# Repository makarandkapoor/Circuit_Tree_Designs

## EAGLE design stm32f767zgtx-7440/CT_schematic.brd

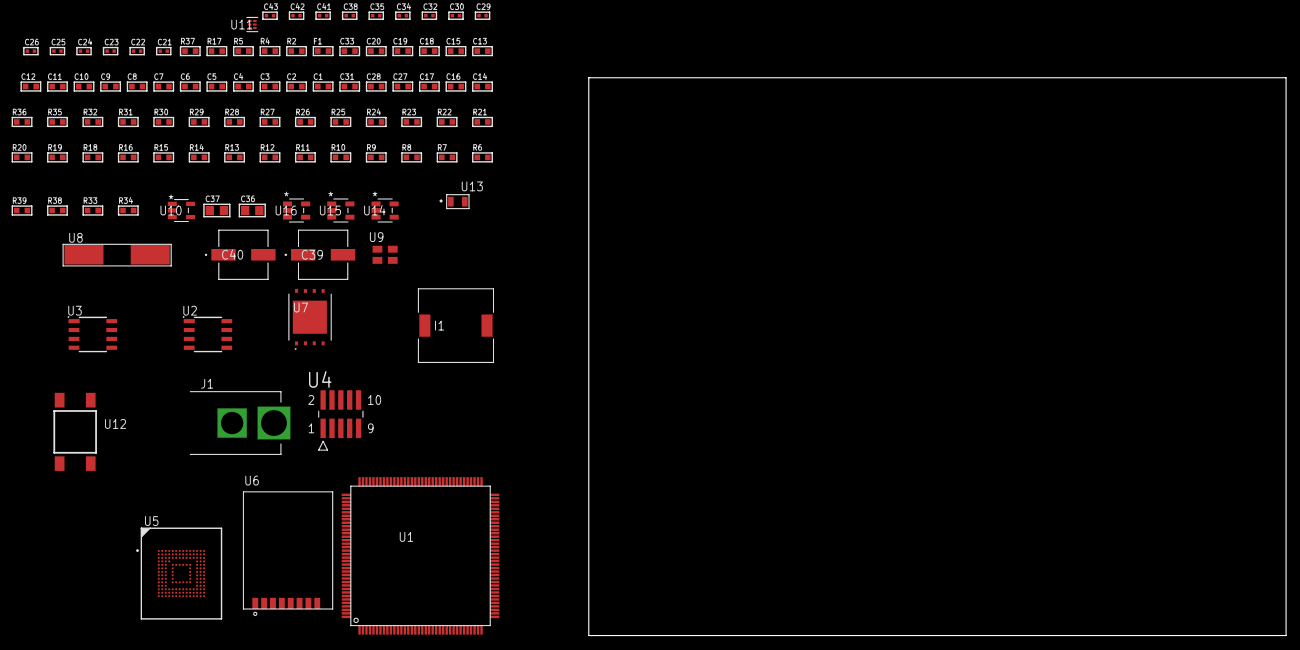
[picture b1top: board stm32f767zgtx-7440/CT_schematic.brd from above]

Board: 2 copper layers, 100.0 x 80.0 mm, 99 parts (0 on the bottom side), 60 nets, no tracks yet.

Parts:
C1, C19, C33: 1e-06; C0603
C2, C3, C4, C5, C6, C7, C8, C9, C10, C11, C12, C13, C15, C20: 1e-07; C0603
C14: 4.7e-06; C0603
C16, C17, C27, C28, C31: 2.2e-06; C0603
C18: 1e-08; C0603
C21, C22: 1e-11; C0402
C23, C24, C34, C35, C41, C42, C43: 1e-08; C0402
C25, C26, C29, C30, C32, C38: 1e-07; C0402
C36, C37: 1e-05; C0805
C39, C40: 0.0001; EXV-9H
F1: 240.0; L0603
I1: 5.2e-06; DR1040
J1: PJ-037B; PJ-037B_PACKAGE
R2: 1000.0; R0603
R4, R5: 4700.0; R0603
R6, R7, R8, R9, R10, R11, R12, R13, R14, R15, R16, R28, R29, R30, R31, R32, R35, R36: 10000.0; R0603
R17: 5.0; R0603
R18, R19, R20, R21, R22, R23, R24, R25, R26, R27: 34000.0; R0603
R33: 220000.0; R0603
R34: 1000000.0; R0603
R37: 9100.0; R0603
R38: 680000.0; R0603
R39: 120000.0; R0603
U1: STM32F767ZGT6; LQFP144
U2: AT25010B-SSHL-T; SOIC-8
U3: AT25M02-SSHD-T; SOIC-8
U4: FTSH-105-01-L-DV-K; SAMTEC_FTSH-105-01-L-DV-K
U5: mtfc4gmcdm; TFBGA-153
U6: RFM75-S
U7: S25FL128SDPNFI001; WNG008
U8: ABLS-25.000MHZ-B2F-T
U9: ASEK-32.768KHz-ECST; ASEK
U10: ltc3406es5; TSOT-23-5
U11: TPS3895ADRYR; SON-6
U12: 4-1437565-2; SW_4-1437565-2
U13: Q65110A2395; LGM67K-G1J2-24-Z
U14, U15, U16: nc7sz125m5x; NC7SZ125M5X

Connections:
CLK_CRYSTAL_U1_23: C21.1, U1.23, U8.1
CLK_CRYSTAL_U1_24: C22.1, U1.24, U8.2
CLK_U1_8: U1.8, U9.3
GND: C1.2, C2.2, C3.2, C4.2, C5.2, C6.2, C7.2, C8.2, C9.2, C10.2, C11.2, C12.2, C13.2, C14.2, C15.2, C16.2, C17.2, C18.2, C19.2, C20.2, C21.2, C22.2, C23.2, C24.2, C25.2, C26.2, C27.2, C28.2, C29.2, C30.2, C31.2, C32.2, C33.2, C34.2, C35.2, C36.2, C37.1, C37.2, C38.2, C39.2, C40.2, C41.2, C42.2, C43.2, J1.2, R2.2, R6.2, R17.2, R33.2, R37.2, R39.2, U1.16, U1.31, U1.38, U1.51, U1.61, U1.83, U1.94, U1.107, U1.120, U1.130, U2.4, U3.4, U4.3, U4.5, U5.C4, U5.E7, U5.G5, U5.H10, U5.K8, U5.N2, U5.N5, U5.P4, U5.P6, U6.1, U7.4, U7.PAD, U9.2, U10.2, U11.2, U13.C, U14.2, U14.3, U15.1, U15.3, U16.1, U16.3
NET_U1_25: R5.1, U1.25, U16.4
NET_U1_33: C18.1, C19.1, F1.1, U1.32, U1.33
NET_U1_71: C16.1, U1.71
NET_U1_106: C17.1, U1.106
NET_U1_138: R6.1, U1.138
NET_U1_142: U12.3, U12.4
NET_U1_143: R7.1, U1.143
NET_U2_3: R8.1, U2.3
NET_U2_7: R10.1, U2.7
NET_U3_3: R11.1, U3.3
NET_U3_7: R13.1, U3.7
NET_U4_9: R17.1, U4.9
NET_U5_C2: C28.1, C29.1, U5.C2
NET_U5_K5: R4.1, U5.K5, U15.4
NET_U6_3: R28.1, U6.3
NET_U7_3: R30.1, U7.3
NET_U7_7: R32.1, U7.7
NET_U10_3: I1.1, U10.3
NET_U10_5: R33.1, R34.1, U10.5
NET_U10_ATNET_3: I1.2, R34.2
NET_U11_1: R36.1, R37.1, U11.1
NET_U11_3: R38.2, R39.1, U11.3
NET_U11_4: R35.1, U11.4, U14.4, U15.2, U16.2
NET_U12_1: R2.1, U12.1, U12.2
PROC_SDMMC1_CK: R27.1, U1.113, U5.M6
PROC_SDMMC1_CMD: R26.1, U1.116, U5.M5
PROC_SDMMC1_D0: R18.1, U1.98, U5.A3
PROC_SDMMC1_D1: R19.1, U1.99, U5.A4
PROC_SDMMC1_D2: R20.1, U1.111, U5.A5
PROC_SDMMC1_D3: R21.1, U1.112, U5.B2
PROC_SDMMC1_D4: R22.1, U1.139, U5.B3
PROC_SDMMC1_D5: R23.1, U1.140, U5.B4
PROC_SDMMC1_D6: R24.1, U1.96, U5.B5
PROC_SDMMC1_D7: R25.1, U1.97, U5.B6
PROC_SPI1_MISO: U1.42, U6.7
PROC_SPI1_MOSI: U1.43, U6.6
PROC_SPI1_NSS: R29.1, U1.40, U6.4
PROC_SPI1_SCK: U1.41, U6.5
PROC_SPI2_MISO: U1.28, U3.2
PROC_SPI2_MOSI: U1.27, U3.5
PROC_SPI2_NSS: R12.1, U1.73, U3.1
PROC_SPI2_SCK: U1.69, U3.6
PROC_SPI4_MISO: U1.4, U7.2
PROC_SPI4_MOSI: U1.5, U7.5
PROC_SPI4_NSS: R31.1, U1.3, U7.1
PROC_SPI4_SCK: U1.1, U7.6
PROC_SPI5_MISO: U1.20, U2.2
PROC_SPI5_MOSI: U1.21, U2.5
PROC_SPI5_NSS: R9.1, U1.18, U2.1
PROC_SPI5_SCK: U1.19, U2.6
PROC_SYS_JTCK_SWCLK: R15.1, U1.109, U4.4
PROC_SYS_JTDO_SWO: U1.133, U4.6
PROC_SYS_JTMS_SWDIO: R16.1, U1.105, U4.2
RST_OUT_U4_JTAG_RST_B: R14.1, U4.10, U14.1
VCC_S1_5V4: C36.1, C39.1, C40.1, J1.1, U10.4
VCC_TIER1_3V3: C1.1, C2.1, C3.1, C4.1, C5.1, C6.1, C7.1, C8.1, C9.1, C10.1, C11.1, C12.1, C13.1, C14.1, C15.1, C20.1, C23.1, C24.1, C25.1, C26.1, C27.1, C30.1, C31.1, C32.1, C33.1, C34.1, C35.1, C37.2, C38.1, C41.1, C42.1, C43.1, F1.2, I1.2, R4.2, R5.2, R7.2, R8.2, R9.2, R10.2, R11.2, R12.2, R13.2, R14.2, R15.2, R16.2, R18.2, R19.2, R20.2, R21.2, R22.2, R23.2, R24.2, R25.2, R26.2, R27.2, R28.2, R29.2, R30.2, R31.2, R32.2, R34.2, R35.2, R36.2, R38.1, U1.6, U1.17, U1.30, U1.39, U1.52, U1.62, U1.72, U1.84, U1.95, U1.108, U1.121, U1.131, U1.144, U2.8, U3.8, U4.1, U5.C6, U5.E6, U5.F5, U5.J10, U5.K9, U5.M4, U5.N4, U5.P3, U5.P5, U6.2, U7.8, U9.4, U11.6, U14.5, U15.5, U16.5

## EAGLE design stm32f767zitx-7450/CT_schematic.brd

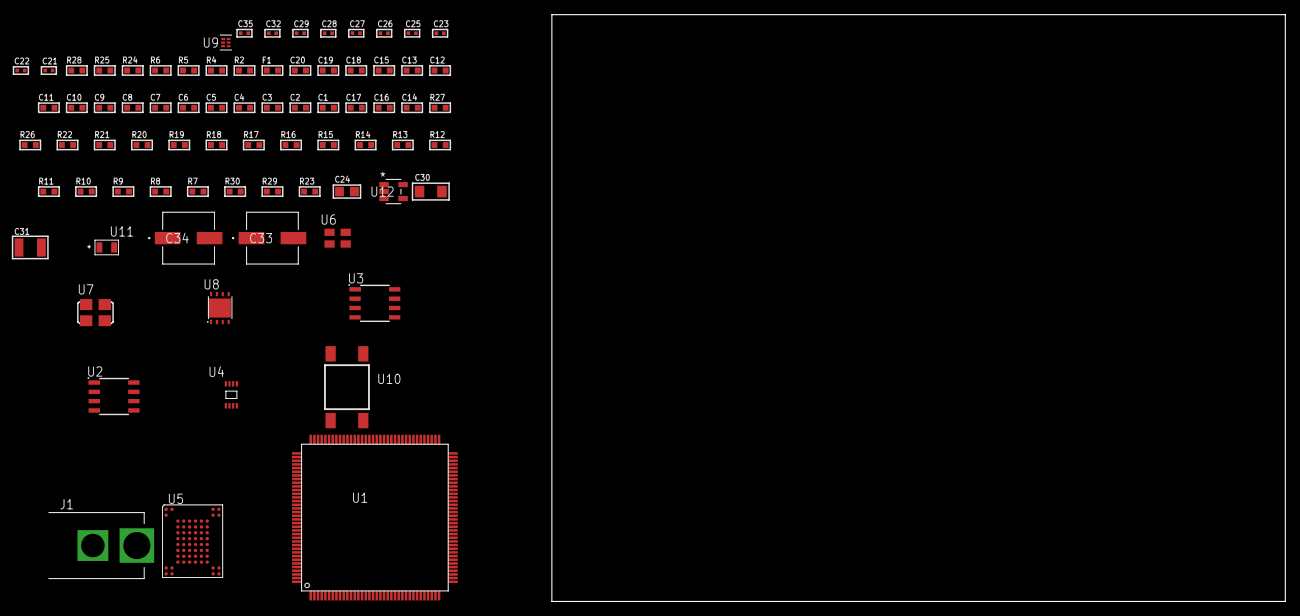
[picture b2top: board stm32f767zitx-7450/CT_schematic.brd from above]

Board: 2 copper layers, 100.0 x 80.0 mm, 77 parts (0 on the bottom side), 51 nets, no tracks yet.

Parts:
C1, C19: 1e-06; C0603
C2, C3, C4, C5, C6, C7, C8, C9, C10, C11, C12, C13, C15, C20: 1e-07; C0603
C14: 4.7e-06; C0603
C16, C17: 2.2e-06; C0603
C18: 1e-08; C0603
C21, C22, C23, C27, C28, C29, C35: 1e-08; C0402
C24: 1e-05; C0805
C25, C26, C32: 1e-07; C0402
C30: 1e-05; C1206
C31: 1e-05; C1210
C33, C34: 0.0001; EXV-9H
F1: 240.0; L0603
J1: PJ-037B; PJ-037B_PACKAGE
R2, R25: 1000.0; R0603
R4: 4700.0; R0603
R5, R6: 2200.0; R0603
R7, R8, R9, R10, R11, R12, R13, R14, R15, R16, R17, R18, R19, R20, R21, R22, R26, R27: 10000.0; R0603
R23: 100000.0; R0603
R24: 2231.0; R0603
R28: 9100.0; R0603
R29: 680000.0; R0603
R30: 120000.0; R0603
U1: STM32F767ZIT6; LQFP144
U2: AT25256B-SSHL-T; SOIC-8
U3: AT25M01-SSHM-T; SOIC-8
U4: 24AA128T-I/MNY; TDFN-8/6MM
U5: TH58NVG3S0HBAI4
U6: ASEK-32.768KHz-ECST; ASEK
U7: ASFL1-25MHZ-NCS; ASFL1
U8: LP3878SDX-ADJ/NOPB; WSON-8
U9: TPS3895ADRYR; SON-6
U10: 4-1437565-2; SW_4-1437565-2
U11: Q65110A2395; LGM67K-G1J2-24-Z
U12: nc7sz125m5x; NC7SZ125M5X

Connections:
CLK_U1_8: U1.8, U6.3
CLK_U1_23: U1.23, U7.3
GND: C1.2, C2.2, C3.2, C4.2, C5.2, C6.2, C7.2, C8.2, C9.2, C10.2, C11.2, C12.2, C13.2, C14.2, C15.2, C16.2, C17.2, C18.2, C19.2, C20.2, C21.2, C22.2, C23.2, C24.2, C25.2, C26.2, C27.2, C28.2, C29.2, C30.2, C31.2, C32.2, C33.2, C34.2, C35.2, J1.2, R2.2, R7.2, R15.2, R25.2, R28.2, R30.2, U1.16, U1.31, U1.38, U1.51, U1.61, U1.83, U1.94, U1.107, U1.120, U1.130, U2.4, U3.4, U4.4, U4.7, U5.C5, U5.K3, U5.K8, U6.2, U7.2, U8.3, U8.PAD, U9.2, U11.C, U12.1, U12.3
NET_U1_25: R4.1, U1.25, U12.4
NET_U1_33: C18.1, C19.1, F1.1, U1.32, U1.33
NET_U1_71: C16.1, U1.71
NET_U1_106: C17.1, U1.106
NET_U1_136: R5.1, U1.136, U4.6
NET_U1_137: R6.1, U1.137, U4.5
NET_U1_138: R7.1, U1.138
NET_U1_142: U10.3, U10.4
NET_U1_143: R8.1, U1.143
NET_U2_3: R9.1, U2.3
NET_U2_7: R11.1, U2.7
NET_U3_3: R12.1, U3.3
NET_U3_7: R14.1, U3.7
NET_U4_1: R15.1, U4.1
NET_U4_2: R16.1, U4.2
NET_U4_3: R17.1, U4.3
NET_U5_C3: R21.1, U5.C3
NET_U8_1: C29.1, U8.1
NET_U8_6: R24.2, R25.1, U8.6
NET_U8_8: R23.1, U8.8
NET_U9_1: R27.1, R28.1, U9.1
NET_U9_3: R29.2, R30.1, U9.3
NET_U9_4: R26.1, U9.4, U12.2
NET_U10_1: R2.1, U10.1, U10.2
PROC_FMC_A16: U1.80, U5.D5
PROC_FMC_A17: U1.81, U5.C4
PROC_FMC_D0: U1.85, U5.H4
PROC_FMC_D1: U1.86, U5.J4
PROC_FMC_D2: U1.114, U5.K4
PROC_FMC_D3: U1.115, U5.K5
PROC_FMC_D4: U1.58, U5.K6
PROC_FMC_D5: U1.59, U5.J7
PROC_FMC_D6: U1.60, U5.K7
PROC_FMC_D7: U1.63, U5.J8
PROC_FMC_INT: R22.1, U1.92, U5.C8
PROC_FMC_NCE: R18.1, U1.98, U5.C6
PROC_FMC_NOE: R19.1, U1.118, U5.D4
PROC_FMC_NWE: R20.1, U1.119, U5.C7
PROC_SPI1_MISO: U1.42, U2.2
PROC_SPI1_MOSI: U1.43, U2.5
PROC_SPI1_NSS: R10.1, U1.40, U2.1
PROC_SPI1_SCK: U1.41, U2.6
PROC_SPI2_MISO: U1.28, U3.2
PROC_SPI2_MOSI: U1.27, U3.5
PROC_SPI2_NSS: R13.1, U1.73, U3.1
PROC_SPI2_SCK: U1.69, U3.6
VCC_S1_6V5: C30.1, C33.1, C34.1, J1.1, R23.2, U8.4
VCC_TIER1_3V3: C1.1, C2.1, C3.1, C4.1, C5.1, C6.1, C7.1, C8.1, C9.1, C10.1, C11.1, C12.1, C13.1, C14.1, C15.1, C20.1, C21.1, C22.1, C23.1, C24.1, C25.1, C26.1, C27.1, C28.1, C31.1, C32.1, C35.1, F1.2, R4.2, R5.2, R6.2, R8.2, R9.2, R10.2, R11.2, R12.2, R13.2, R14.2, R16.2, R17.2, R18.2, R19.2, R20.2, R21.2, R22.2, R24.1, R26.2, R27.2, R29.1, U1.6, U1.17, U1.30, U1.39, U1.52, U1.62, U1.72, U1.84, U1.95, U1.108, U1.121, U1.131, U1.144, U2.8, U3.8, U4.8, U5.H8, U5.J6, U6.4, U7.4, U8.5, U9.6, U12.5

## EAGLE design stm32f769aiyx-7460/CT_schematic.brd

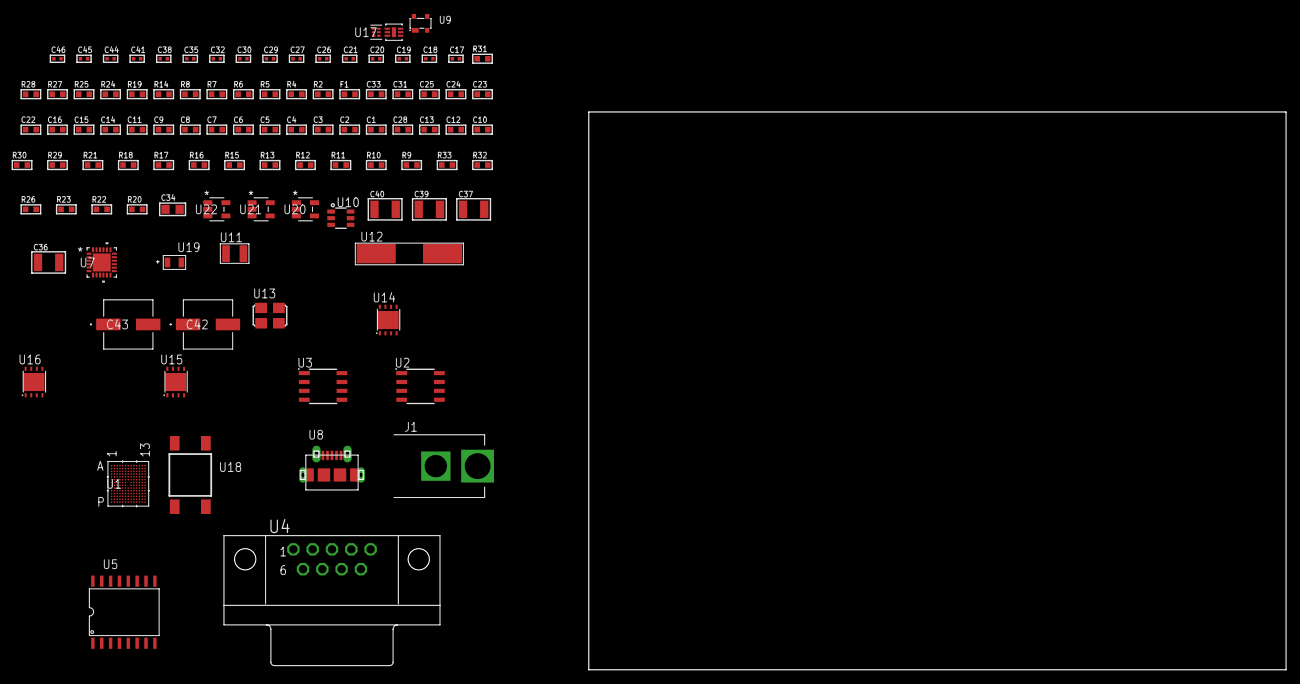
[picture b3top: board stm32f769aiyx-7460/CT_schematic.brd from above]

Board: 2 copper layers, 101 parts (0 on the bottom side), 70 nets, no tracks yet.

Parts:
C1, C15, C22, C23, C24, C25, C31: 1e-06; C0603
C2, C3, C4, C5, C6, C7, C8, C9, C11, C16: 1e-07; C0603
C10: 4.7e-06; C0603
C12, C13, C28: 2.2e-06; C0603
C14: 1e-08; C0603
C17, C18, C19, C20: 1e-11; C0402
C21, C27, C29, C30, C32, C35, C38, C44, C45, C46: 1e-08; C0402
C26, C41: 1e-07; C0402
C33: 8e-07; R0603
C34: 1e-05; C0805
C36, C37, C39, C40: 1e-05; C1210
C42, C43: 0.0001; EXV-9H
F1: 240.0; L0603
J1: PJ-037B; PJ-037B_PACKAGE
R2, R25, R28: 1000.0; R0603
R4, R5, R6: 4700.0; R0603
R7, R8: 2200.0; R0603
R9, R10, R11, R12, R13, R15, R16, R17, R29, R30: 10000.0; R0603
R14: 120.0; R0603
R18: 47000.0; R0603
R19: 8060.0; R0603
R20, R22, R23, R26: 100000.0; R0603
R21: 36000.0; R0603
R24: 2231.0; R0603
R27: 3900.0; R0603
R31: 9100.0; R0603
R32: 680000.0; R0603
R33: 120000.0; R0603
U1: STM32F769AIY6TR; WLCSP180
U2: AT25040B-SSHL-T; SOIC-8
U3: MCP2562-E/SN; SOIC-8
U4: 182-009-113R531; 182-009-MALE
U5: S25FL128SDSMFI000
U6: SI7006-A20-IM; DFN-6
U7: USB3317C-CP-TR; QFN-24
U8: 47590-0001; MICRO_USB_AB
U9: prtr5v0u2ax; SOT143B
U10: MAX4995AAUT+T; SOT-23-6
U11: ABS07-32.768KHZ-7-T
U12: ABLS-25.000MHZ-B2F-T
U13: ASFL1-26MHZ-NCS; ASFL1
U14: LP2951ACSDX/NOPB; WSON-8
U15, U16: LP3878SDX-ADJ/NOPB; WSON-8
U17: TPS3895ADRYR; SON-6
U18: 4-1437565-2; SW_4-1437565-2
U19: Q65110A2395; LGM67K-G1J2-24-Z
U20, U21, U22: nc7sz125m5x; NC7SZ125M5X

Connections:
CLK_CRYSTAL_U1_E12: C17.1, U1.E12, U11.1
CLK_CRYSTAL_U1_E13: C18.1, U1.E13, U11.2
CLK_CRYSTAL_U1_K12: C19.1, U1.K12, U12.1
CLK_CRYSTAL_U1_K13: C20.1, U1.K13, U12.2
CLK_U7_23: U7.23, U13.3
GND: C1.2, C2.2, C3.2, C4.2, C5.2, C6.2, C7.2, C8.2, C9.2, C10.2, C11.2, C12.2, C13.2, C14.2, C15.2, C16.2, C17.2, C18.2, C19.2, C20.2, C21.2, C22.2, C23.2, C24.2, C25.2, C26.2, C27.2, C28.2, C29.2, C30.2, C31.2, C32.2, C33.2, C34.2, C35.2, C36.2, C37.2, C38.2, C39.2, C40.2, C41.2, C42.2, C43.2, C44.2, C45.2, C46.2, J1.2, R2.2, R9.2, R18.2, R19.2, R22.2, R25.2, R28.2, R31.2, R33.2, U1.A8, U1.A11, U1.B6, U1.C2, U1.F1, U1.F13, U1.H5, U1.J9, U1.J13, U1.M1, U1.M11, U1.N4, U1.N5, U1.P9, U2.4, U3.2, U3.8, U4.5, U5.10, U6.2, U6.7, U7.25, U8.5, U8.6, U8.7, U8.8, U8.9, U9.1, U10.2, U13.2, U14.3, U14.4, U14.PAD, U15.3, U15.PAD, U16.3, U16.PAD, U17.2, U19.C, U20.1, U20.3, U21.1, U21.3, U22.1, U22.3
NET_U1_A10: R9.1, U1.A10
NET_U1_C1: C13.1, U1.C1
NET_U1_C8: R8.1, U1.C8, U6.1
NET_U1_C10: R10.1, U1.C10
NET_U1_E9: R7.1, U1.E9, U6.6
NET_U1_L11: R5.1, U1.L11, U21.4
NET_U1_M12: C14.1, C15.1, F1.1, U1.M12
NET_U1_P5: C12.1, U1.P5
NET_U1_P8: U18.3, U18.4
NET_U2_3: R11.1, U2.3
NET_U2_7: R13.1, U2.7
NET_U3_6: R14.2, U3.6
NET_U4_2: R14.2, U3.6, U4.2
NET_U4_3: R14.1, U3.7, U4.3
NET_U5_3: R4.1, U5.3, U20.4
NET_U7_4: C28.1, U7.4
NET_U7_22: R6.1, U7.22, U22.4
NET_U7_24: R19.1, U7.24
NET_U8_1: C31.1, U7.2, U8.1, U9.4, U10.1
NET_U8_2: U7.5, U8.2, U9.3
NET_U8_3: U7.6, U8.3, U9.2
NET_U8_4: U7.1, U8.4
NET_U10_3: R18.1, U10.3
NET_U10_4: U7.7, U10.4
NET_U14_5: R20.1, U14.5
NET_U14_7: R21.2, R22.1, U14.7
NET_U15_1: C35.1, U15.1
NET_U15_6: R24.2, R25.1, U15.6
NET_U15_8: R23.1, U15.8
NET_U16_1: C38.1, U16.1
NET_U16_6: R27.2, R28.1, U16.6
NET_U16_8: R26.1, U16.8
NET_U17_1: R30.1, R31.1, U17.1
NET_U17_3: R32.2, R33.1, U17.3
NET_U17_4: R29.1, U17.4, U20.2, U21.2, U22.2
NET_U18_1: R2.1, U18.1, U18.2
PROC_CAN1_RX: U1.A4, U3.4
PROC_CAN1_TX: U1.D1, U3.1
PROC_QUADSPI_BK1_IO0: U1.E1, U5.15
PROC_QUADSPI_BK1_IO1: U1.B4, U5.8
PROC_QUADSPI_BK1_IO2: R16.1, U1.E10, U5.9
PROC_QUADSPI_BK1_IO3: R17.1, U1.J11, U5.1
PROC_QUADSPI_BK1_NCS: R15.1, U1.B9, U5.7
PROC_QUADSPI_CLK: U1.J7, U5.16
PROC_SPI1_MISO: U1.C6, U2.2
PROC_SPI1_MOSI: U1.E7, U2.5
PROC_SPI1_NSS: R12.1, U1.A7, U2.1
PROC_SPI1_SCK: U1.B7, U2.6
PROC_USB_OTG_HS_ULPI_CK: U1.P11, U7.12
PROC_USB_OTG_HS_ULPI_D0: U1.M10, U7.16
PROC_USB_OTG_HS_ULPI_D1: U1.P10, U7.15
PROC_USB_OTG_HS_ULPI_D2: U1.J8, U7.14
PROC_USB_OTG_HS_ULPI_D3: U1.K5, U7.13
PROC_USB_OTG_HS_ULPI_D4: U1.L5, U7.11
PROC_USB_OTG_HS_ULPI_D5: U1.H8, U7.10
PROC_USB_OTG_HS_ULPI_D6: U1.J5, U7.9
PROC_USB_OTG_HS_ULPI_D7: U1.A9, U7.8
PROC_USB_OTG_HS_ULPI_DIR: U1.F11, U7.19
PROC_USB_OTG_HS_ULPI_NXT: U1.N12, U7.18
PROC_USB_OTG_HS_ULPI_STP: U1.L12, U7.20
VCC_S1_12V4: C33.1, C36.1, C39.1, C42.1, C43.1, J1.1, R23.2, R26.2, U14.8, U15.4, U16.4
VCC_TIER1_1V8: C21.1, C30.1, C34.1, C44.1, C45.1, C46.1, R11.2, R12.2, R13.2, R20.2, R21.1, U2.8, U7.21, U14.1, U20.5, U21.5, U22.5
VCC_TIER1_3V3: C1.1, C2.1, C3.1, C4.1, C5.1, C6.1, C7.1, C8.1, C9.1, C10.1, C11.1, C16.1, C23.1, C24.1, C25.1, C26.1, C27.1, C29.1, C32.1, C37.1, C41.1, F1.2, R4.2, R5.2, R6.2, R7.2, R8.2, R10.2, R15.2, R16.2, R17.2, R24.1, R29.2, R30.2, R32.1, U1.A6, U1.B2, U1.B8, U1.B11, U1.C13, U1.F2, U1.F12, U1.J12, U1.K1, U1.K9, U1.M8, U1.P4, U3.5, U5.2, U5.14, U6.5, U7.3, U7.17, U13.4, U15.5, U17.6
VCC_TIER1_5V0: C22.1, C40.1, R27.1, U3.3, U10.5, U16.5

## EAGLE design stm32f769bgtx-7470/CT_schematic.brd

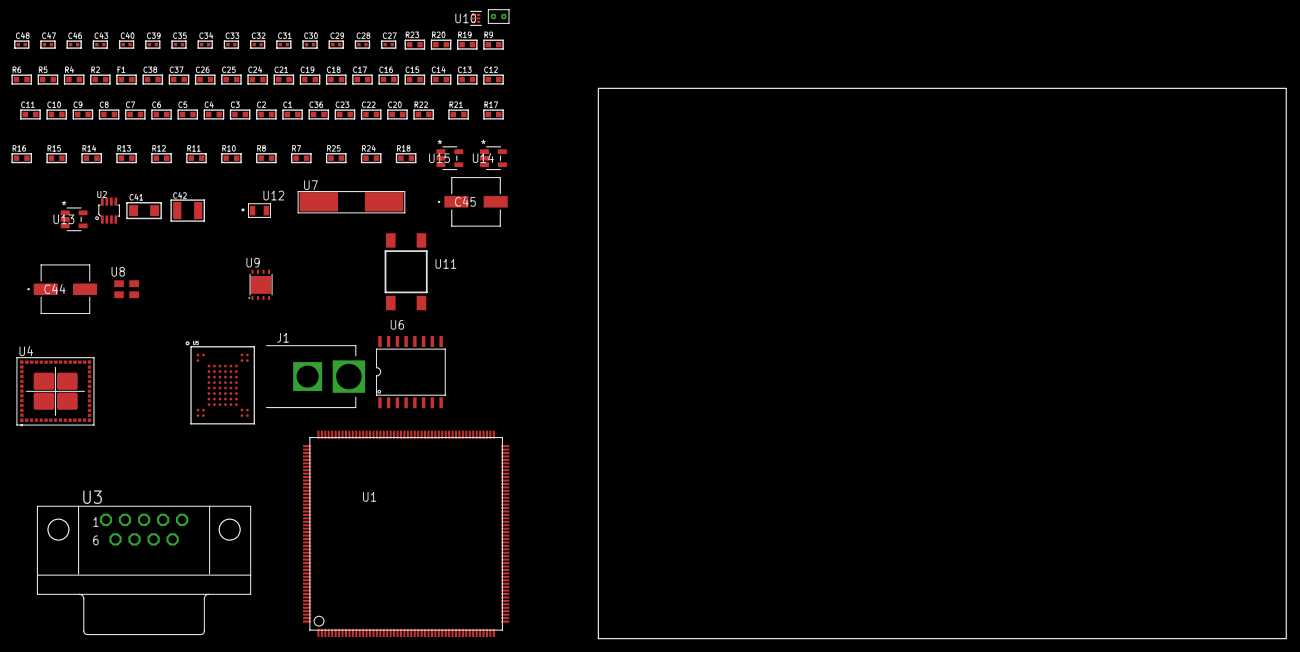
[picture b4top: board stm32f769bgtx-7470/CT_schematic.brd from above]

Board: 2 copper layers, 100.0 x 80.0 mm, 89 parts (0 on the bottom side), 53 nets, no tracks yet.

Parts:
C1, C25, C37, C38: 1e-06; C0603
C2, C3, C4, C5, C6, C7, C8, C9, C10, C11, C12, C13, C14, C15, C16, C17, C18, C19, C21, C26: 1e-07; C0603
C20: 4.7e-06; C0603
C22, C23, C36: 2.2e-06; C0603
C24: 1e-08; C0603
C27, C28: 1e-11; C0402
C29, C30, C31, C32, C33, C34, C35, C43: 1e-07; C0402
C39, C40, C46, C47, C48: 1e-08; C0402
C41: 1e-05; C1206
C42: 1e-05; C1210
C44, C45: 0.0001; EXV-9H
F1: 240.0; L0603
J1: PJ-037B; PJ-037B_PACKAGE
R2, R20: 1000.0; R0603
R4, R5, R6: 4700.0; R0603
R7, R8, R10, R11, R12, R13, R14, R15, R16, R17, R21, R22: 10000.0; R0603
R9: 120.0; R0603
R18: 100000.0; R0603
R19: 2231.0; R0603
R23: 9100.0; R0603
R24: 680000.0; R0603
R25: 120000.0; R0603
U1: STM32F769BGT6; LQFP208
U2: MAX3051EKA+T; SOT-23-8
U3: 182-009-113R531; 182-009-MALE
U4: MBH7BLZ02-109004
U5: mt29f4g08abadah4; VFBGA-63
U6: S25FL128SDSMFI000
U7: ABLS-25.000MHZ-B2F-T
U8: ASEK-32.768KHz-ECST; ASEK
U9: LP3878SDX-ADJ/NOPB; WSON-8
U10: TPS3895ADRYR; SON-6
U11: 4-1437565-2; SW_4-1437565-2
U12: Q65110A2395; LGM67K-G1J2-24-Z
U13, U14, U15: nc7sz125m5x; NC7SZ125M5X
U16: Dummy; DUMMY_PACKAGE_198

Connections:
CLK_CRYSTAL_U1_32: C27.1, U1.32, U7.1
CLK_CRYSTAL_U1_33: C28.1, U1.33, U7.2
CLK_U1_9: U1.9, U8.3
GND: C1.2, C2.2, C3.2, C4.2, C5.2, C6.2, C7.2, C8.2, C9.2, C10.2, C11.2, C12.2, C13.2, C14.2, C15.2, C16.2, C17.2, C18.2, C19.2, C20.2, C21.2, C22.2, C23.2, C24.2, C25.2, C26.2, C27.2, C28.2, C29.2, C30.2, C31.2, C32.2, C33.2, C34.2, C35.2, C36.2, C37.2, C38.2, C39.2, C40.2, C41.2, C42.2, C43.2, C44.2, C45.2, C46.2, C47.2, C48.2, J1.2, R2.2, R7.2, R20.2, R23.2, R25.2, U1.14, U1.25, U1.40, U1.51, U1.60, U1.72, U1.82, U1.93, U1.114, U1.122, U1.128, U1.136, U1.149, U1.170, U1.184, U1.202, U2.2, U2.8, U3.5, U4.1, U4.3, U4.15, U4.27, U4.29, U4.41, U4.42, U4.43, U4.44, U4.45, U4.46, U4.47, U4.48, U4.49, U4.50, U4.52, U4.53, U4.54, U4.55, U4.56, U5.C5, U5.F7, U5.K3, U5.K8, U6.10, U8.2, U9.3, U9.PAD, U10.2, U12.C, U13.1, U13.3, U14.1, U14.3, U15.1, U15.3, U16.1
NET_U1_34: R6.1, U1.34, U15.4
NET_U1_42: C24.1, C25.1, F1.1, U1.41, U1.42
NET_U1_92: C22.1, U1.92
NET_U1_148: C23.1, U1.148
NET_U1_197: R7.1, U1.197
NET_U1_203: R8.1, U1.203
NET_U1_208: U11.3, U11.4
NET_U2_6: R9.2, U2.6
NET_U3_2: R9.2, U2.6, U3.2
NET_U3_3: R9.1, U2.7, U3.3
NET_U4_39: R5.1, U4.39, U14.4
NET_U5_C3: R14.1, U5.C3
NET_U6_3: R4.1, U6.3, U13.4
NET_U9_1: C40.1, U9.1
NET_U9_6: R19.2, R20.1, U9.6
NET_U9_8: R18.1, U9.8
NET_U10_1: R22.1, R23.1, U10.1
NET_U10_3: R24.2, R25.1, U10.3
NET_U10_4: R21.1, U10.4, U13.2, U14.2, U15.2
NET_U11_1: R2.1, U11.1, U11.2
PROC_CAN1_RX: U1.11, U2.4
PROC_CAN1_TX: U1.146, U2.1
PROC_DAC_OUT2: U1.54, U16.2
PROC_FMC_A16: U1.111, U5.D5
PROC_FMC_A17: U1.112, U5.C4
PROC_FMC_D0: U1.116, U5.H4
PROC_FMC_D1: U1.117, U5.J4
PROC_FMC_D2: U1.164, U5.K4
PROC_FMC_D3: U1.165, U5.K5
PROC_FMC_D4: U1.79, U5.K6
PROC_FMC_D5: U1.80, U5.J7
PROC_FMC_D6: U1.81, U5.K7
PROC_FMC_D7: U1.84, U5.J8
PROC_FMC_INT: R10.1, U1.134, U5.C8
PROC_FMC_NCE: R11.1, U1.140, U5.C6
PROC_FMC_NOE: R13.1, U1.168, U5.D4
PROC_FMC_NWE: R12.1, U1.169, U5.C7
PROC_QUADSPI_BK1_IO0: U1.29, U6.15
PROC_QUADSPI_BK1_IO1: U1.30, U6.8
PROC_QUADSPI_BK1_IO2: R16.1, U1.1, U6.9
PROC_QUADSPI_BK1_IO3: R17.1, U1.27, U6.1
PROC_QUADSPI_BK1_NCS: R15.1, U1.90, U6.7
PROC_QUADSPI_CLK: U1.31, U6.16
PROC_UART4_CTS: U1.61, U4.26
PROC_UART4_RTS: U1.106, U4.24
PROC_UART4_RX: U1.44, U4.25
PROC_UART4_TX: U1.43, U4.23
VCC_S1_7V0: C41.1, C44.1, C45.1, J1.1, R18.2, U9.4
VCC_TIER1_3V3: C1.1, C2.1, C3.1, C4.1, C5.1, C6.1, C7.1, C8.1, C9.1, C10.1, C11.1, C12.1, C13.1, C14.1, C15.1, C16.1, C17.1, C18.1, C19.1, C20.1, C21.1, C26.1, C29.1, C30.1, C31.1, C32.1, C33.1, C34.1, C35.1, C36.1, C37.1, C38.1, C39.1, C42.1, C43.1, C46.1, C47.1, C48.1, F1.2, R4.2, R5.2, R6.2, R8.2, R10.2, R11.2, R12.2, R13.2, R14.2, R15.2, R16.2, R17.2, R19.1, R21.2, R22.2, R24.1, U1.6, U1.15, U1.26, U1.39, U1.52, U1.59, U1.73, U1.83, U1.94, U1.103, U1.115, U1.118, U1.137, U1.150, U1.158, U1.171, U1.185, U1.204, U2.3, U4.28, U5.D3, U5.G4, U5.H8, U5.J6, U6.2, U6.14, U8.4, U9.5, U10.6, U13.5, U14.5, U15.5

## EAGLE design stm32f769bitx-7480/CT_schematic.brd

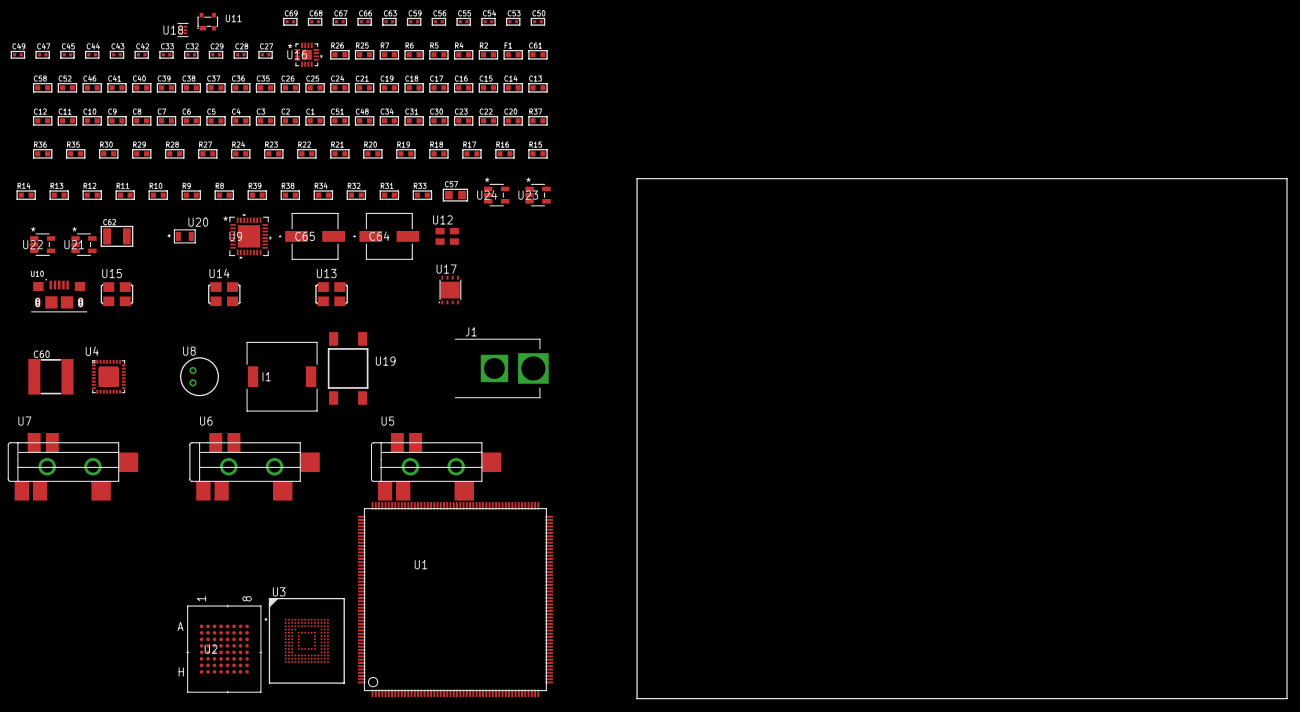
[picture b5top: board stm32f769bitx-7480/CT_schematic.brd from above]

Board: 2 copper layers, 133 parts (0 on the bottom side), 122 nets, no tracks yet.

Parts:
C1, C25, C35, C36, C37, C38, C39, C40, C41, C46, C52, C58, C61: 1e-06; C0603
C2, C3, C4, C5, C6, C7, C8, C9, C10, C11, C12, C13, C14, C15, C16, C17, C18, C19, C21, C26: 1e-07; C0603
C20: 4.7e-06; C0603
C22, C23, C30, C31, C34, C48, C51: 2.2e-06; C0603
C24: 1e-08; C0603
C27, C28, C53, C54, C55, C56, C66, C67, C68, C69: 1e-08; C0402
C29, C32, C33, C42, C43, C44, C45, C47, C49, C50, C59, C63: 1e-07; C0402
C57: 1e-05; C0805
C60: 6.8e-05; 2220
C62: 1e-05; C1210
C64, C65: 0.0001; EXV-9H
F1: 240.0; L0603
I1: 3.8e-06; DR1040
J1: PJ-037B; PJ-037B_PACKAGE
R2: 1000.0; R0603
R4, R5, R6, R7: 4700.0; R0603
R8, R9, R10, R11, R12, R13, R14, R27, R28, R35, R36: 10000.0; R0603
R15, R16, R17, R18, R19, R20, R21, R22, R23, R24: 34000.0; R0603
R25, R26: 1270.0; R0603
R29: 20000.0; R0603
R30: 39000.0; R0603
R31, R38: 300000.0; R0603
R32, R34: 100000.0; R0603
R33: 153694.38; R0603
R37: 82000.0; R0603
R39: 120000.0; R0603
U1: STM32F769BIT6; LQFP208
U2: mt28ew256aba1HPC-0SIT; LBGA-64
U3: mtfc4gmcdm; TFBGA-153
U4: SGTL5000XNAA3; QFN-32
U5, U6, U7: SJ-43515TS-SMT-TR
U8: WM-64PCT; WM-64PC
U9: TUSB1210BRHBR; RHB32_3P45X3P45
U10: 10118193-0001LF; FCI_10118193-0001LF
U11: prtr5v0u2ax; SOT143B
U12: ASEK-32.768KHz-ECST; ASEK
U13: ASFL-24.57MHZ-NCS; ASFL1
U14: ASFL1-25MHZ-NCS; ASFL1
U15: ASFL1-26MHZ-NCS; ASFL1
U16: LTC3601EUD#PBF; QFN-16_EP
U17: LP2951ACSDX/NOPB; WSON-8
U18: TPS3895ADRYR; SON-6
U19: 4-1437565-2; SW_4-1437565-2
U20: Q65110A2395; LGM67K-G1J2-24-Z
U21, U22, U23, U24: nc7sz125m5x; NC7SZ125M5X

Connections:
CLK_U1_9: U1.9, U12.3
CLK_U1_32: U1.32, U14.3
CLK_U4_21: U4.21, U13.3
CLK_U9_1: U9.1, U15.3
GND: C1.2, C2.2, C3.2, C4.2, C5.2, C6.2, C7.2, C8.2, C9.2, C10.2, C11.2, C12.2, C13.2, C14.2, C15.2, C16.2, C17.2, C18.2, C19.2, C20.2, C21.2, C22.2, C23.2, C24.2, C25.2, C26.2, C27.2, C28.2, C29.2, C30.2, C31.2, C32.2, C33.2, C34.2, C42.2, C43.2, C44.2, C45.2, C46.2, C47.2, C48.2, C49.2, C50.2, C51.2, C52.2, C53.2, C54.2, C55.2, C56.2, C57.2, C58.2, C60.1, C60.2, C61.2, C62.2, C63.2, C64.2, C65.2, C66.2, C67.2, C68.2, C69.2, J1.2, R2.2, R8.2, R26.2, R29.2, R31.2, R34.2, R37.2, R39.2, U1.14, U1.25, U1.40, U1.51, U1.60, U1.72, U1.82, U1.93, U1.114, U1.122, U1.128, U1.136, U1.149, U1.170, U1.184, U1.202, U2.E8, U2.H2, U2.H7, U3.C4, U3.E7, U3.G5, U3.H10, U3.K8, U3.N2, U3.N5, U3.P4, U3.P6, U4.1, U4.3, U4.7, U4.EXP, U6.1, U7.1, U8.2, U9.33, U10.5, U10.6, U10.7, U10.8, U10.9, U11.1, U12.2, U13.2, U14.2, U15.2, U16.1, U16.9, U16.17, U17.3, U17.4, U17.PAD, U18.2, U20.C, U21.1, U21.3, U22.1, U22.3, U23.1, U23.3, U24.1, U24.3
NET_U1_34: R6.1, U1.34, U23.4
NET_U1_42: C24.1, C25.1, F1.1, U1.41, U1.42
NET_U1_92: C22.1, U1.92
NET_U1_148: C23.1, U1.148
NET_U1_197: R8.1, U1.197
NET_U1_203: R9.1, U1.203
NET_U1_208: U19.3, U19.4
NET_U2_B4: R13.1, U2.B4
NET_U2_B5: R4.1, U2.B5, U21.4
NET_U3_C2: C31.1, C32.1, U3.C2
NET_U3_K5: R5.1, U3.K5, U22.4
NET_U4_10: C45.1, U4.10
NET_U4_29: R25.1, U4.29
NET_U4_31: R26.1, U4.31
NET_U5_1: U4.4, U5.1
NET_U5_2: U4.2, U5.2
NET_U5_5: U4.6, U5.5
NET_U6_2: C36.1, U6.2
NET_U6_5: C35.1, U6.5
NET_U7_2: C38.1, C39.1, U7.2
NET_U7_5: C37.1, U7.5
NET_U7_13: C38.2, C39.2
NET_U8_1: C40.1, C41.1, C46.1, U4.16, U8.1
NET_U8_15: C40.2, C41.2
NET_U9_11: R27.1, U9.11
NET_U9_12: C51.1, U9.12
NET_U9_14: R28.1, U9.14
NET_U9_20: C48.1, U9.20
NET_U9_27: R7.1, U9.27, U24.4
NET_U10_1: C52.1, U9.22, U10.1, U11.4
NET_U10_2: U9.19, U10.2, U11.3
NET_U10_3: U9.18, U10.3, U11.2
NET_U16_3: C59.2, I1.1, U16.3, U16.4
NET_U16_6: C59.1, U16.6
NET_U16_7: C58.1, U16.7, U16.12
NET_U16_10: R31.1, U16.10
NET_U16_11: R29.1, R30.1, U16.11
NET_U16_ATNET_3: I1.2, R30.2
NET_U17_5: R32.1, U17.5
NET_U17_7: R33.2, R34.1, U17.7
NET_U18_1: R36.1, R37.1, U18.1
NET_U18_3: R38.2, R39.1, U18.3
NET_U18_4: R35.1, U18.4, U21.2, U22.2, U23.2, U24.2
NET_U19_1: R2.1, U19.1, U19.2
PROC_FMC_A0: U1.16, U2.E2
PROC_FMC_A1: U1.17, U2.D2
PROC_FMC_A2: U1.18, U2.C2
PROC_FMC_A3: U1.22, U2.A2
PROC_FMC_A4: U1.23, U2.B2
PROC_FMC_A5: U1.24, U2.D3
PROC_FMC_A6: U1.71, U2.C3
PROC_FMC_A7: U1.74, U2.A3
PROC_FMC_A8: U1.75, U2.B6
PROC_FMC_A9: U1.76, U2.A6
PROC_FMC_A10: U1.77, U2.C6
PROC_FMC_A11: U1.78, U2.D6
PROC_FMC_A12: U1.129, U2.B7
PROC_FMC_A13: U1.130, U2.A7
PROC_FMC_A14: U1.131, U2.C7
PROC_FMC_A15: U1.132, U2.D7
PROC_FMC_A16: U1.111, U2.E7
PROC_FMC_A17: U1.112, U2.B3
PROC_FMC_A18: U1.113, U2.C4
PROC_FMC_A19: U1.2, U2.D5
PROC_FMC_A20: U1.3, U2.D4
PROC_FMC_A21: U1.4, U2.C5
PROC_FMC_A22: U1.5, U2.B8
PROC_FMC_A23: U1.1, U2.C8
PROC_FMC_D0: U1.116, U2.E3
PROC_FMC_D1: U1.117, U2.H3
PROC_FMC_D2: U1.164, U2.E4
PROC_FMC_D3: U1.165, U2.H4
PROC_FMC_D4: U1.79, U2.H5
PROC_FMC_D5: U1.80, U2.E5
PROC_FMC_D6: U1.81, U2.H6
PROC_FMC_D7: U1.84, U2.E6
PROC_FMC_D8: U1.85, U2.F3
PROC_FMC_D9: U1.86, U2.G3
PROC_FMC_D10: U1.87, U2.F4
PROC_FMC_D11: U1.88, U2.G4
PROC_FMC_D12: U1.89, U2.F5
PROC_FMC_D13: U1.108, U2.G6
PROC_FMC_D14: U1.109, U2.F6
PROC_FMC_D15: U1.110, U2.G7
PROC_FMC_NBL0: R14.1, U1.200, U2.F7
PROC_FMC_NE2: R10.1, U1.178, U2.F2
PROC_FMC_NOE: R11.1, U1.168, U2.G2
PROC_FMC_NWAIT: U1.172, U2.A4
PROC_FMC_NWE: R12.1, U1.169, U2.A5
PROC_I2S1_CK: U1.180, U4.24
PROC_I2S1_SD: U1.56, U4.26
PROC_I2S1_WS: U1.53, U4.23
PROC_SDMMC1_CK: R24.1, U1.163, U3.M6
PROC_SDMMC1_CMD: R23.1, U1.166, U3.M5
PROC_SDMMC1_D0: R15.1, U1.140, U3.A3
PROC_SDMMC1_D1: R16.1, U1.141, U3.A4
PROC_SDMMC1_D2: R17.1, U1.161, U3.A5
PROC_SDMMC1_D3: R18.1, U1.162, U3.B2
PROC_SDMMC1_D4: R19.1, U1.198, U3.B3
PROC_SDMMC1_D5: R20.1, U1.199, U3.B4
PROC_SDMMC1_D6: R21.1, U1.138, U3.B5
PROC_SDMMC1_D7: R22.1, U1.139, U3.B6
PROC_USB_OTG_HS_ULPI_CK: U1.54, U9.26
PROC_USB_OTG_HS_ULPI_D0: U1.50, U9.3
PROC_USB_OTG_HS_ULPI_D1: U1.61, U9.4
PROC_USB_OTG_HS_ULPI_D2: U1.62, U9.5
PROC_USB_OTG_HS_ULPI_D3: U1.90, U9.6
PROC_USB_OTG_HS_ULPI_D4: U1.91, U9.7
PROC_USB_OTG_HS_ULPI_D5: U1.104, U9.9
PROC_USB_OTG_HS_ULPI_D6: U1.105, U9.10
PROC_USB_OTG_HS_ULPI_D7: U1.194, U9.13
PROC_USB_OTG_HS_ULPI_DIR: U1.13, U9.31
PROC_USB_OTG_HS_ULPI_NXT: U1.38, U9.2
PROC_USB_OTG_HS_ULPI_STP: U1.35, U9.29
VCC_S1_6V7: C57.1, C61.1, C64.1, C65.1, J1.1, U16.15, U16.16, U17.8
VCC_TIER1_1V8: C1.1, C2.1, C3.1, C4.1, C5.1, C6.1, C7.1, C8.1, C9.1, C10.1, C11.1, C12.1, C13.1, C14.1, C15.1, C16.1, C17.1, C18.1, C19.1, C20.1, C21.1, C27.1, C29.1, C30.1, C42.1, C43.1, C44.1, C49.1, C50.1, C60.2, C63.1, C66.1, C67.1, C68.1, C69.1, F1.2, I1.2, R4.2, R5.2, R6.2, R7.2, R9.2, R10.2, R11.2, R12.2, R13.2, R14.2, R15.2, R16.2, R17.2, R18.2, R19.2, R20.2, R21.2, R22.2, R23.2, R24.2, R25.2, R27.2, R28.2, R30.2, R35.2, R36.2, R38.1, U1.6, U1.15, U1.26, U1.39, U1.52, U1.59, U1.73, U1.83, U1.94, U1.103, U1.115, U1.118, U1.150, U1.158, U1.171, U1.185, U1.204, U2.D8, U2.F1, U3.C6, U3.M4, U3.N4, U3.P3, U3.P5, U4.5, U4.20, U4.30, U9.28, U9.30, U9.32, U16.8, U18.6, U21.5, U22.5, U23.5, U24.5
VCC_TIER1_3V3: C26.1, C28.1, C33.1, C34.1, C47.1, C53.1, C54.1, C55.1, C56.1, C62.1, R32.2, R33.1, U1.137, U2.G5, U3.E6, U3.F5, U3.J10, U3.K9, U9.21, U12.4, U13.4, U14.4, U15.4, U17.1
